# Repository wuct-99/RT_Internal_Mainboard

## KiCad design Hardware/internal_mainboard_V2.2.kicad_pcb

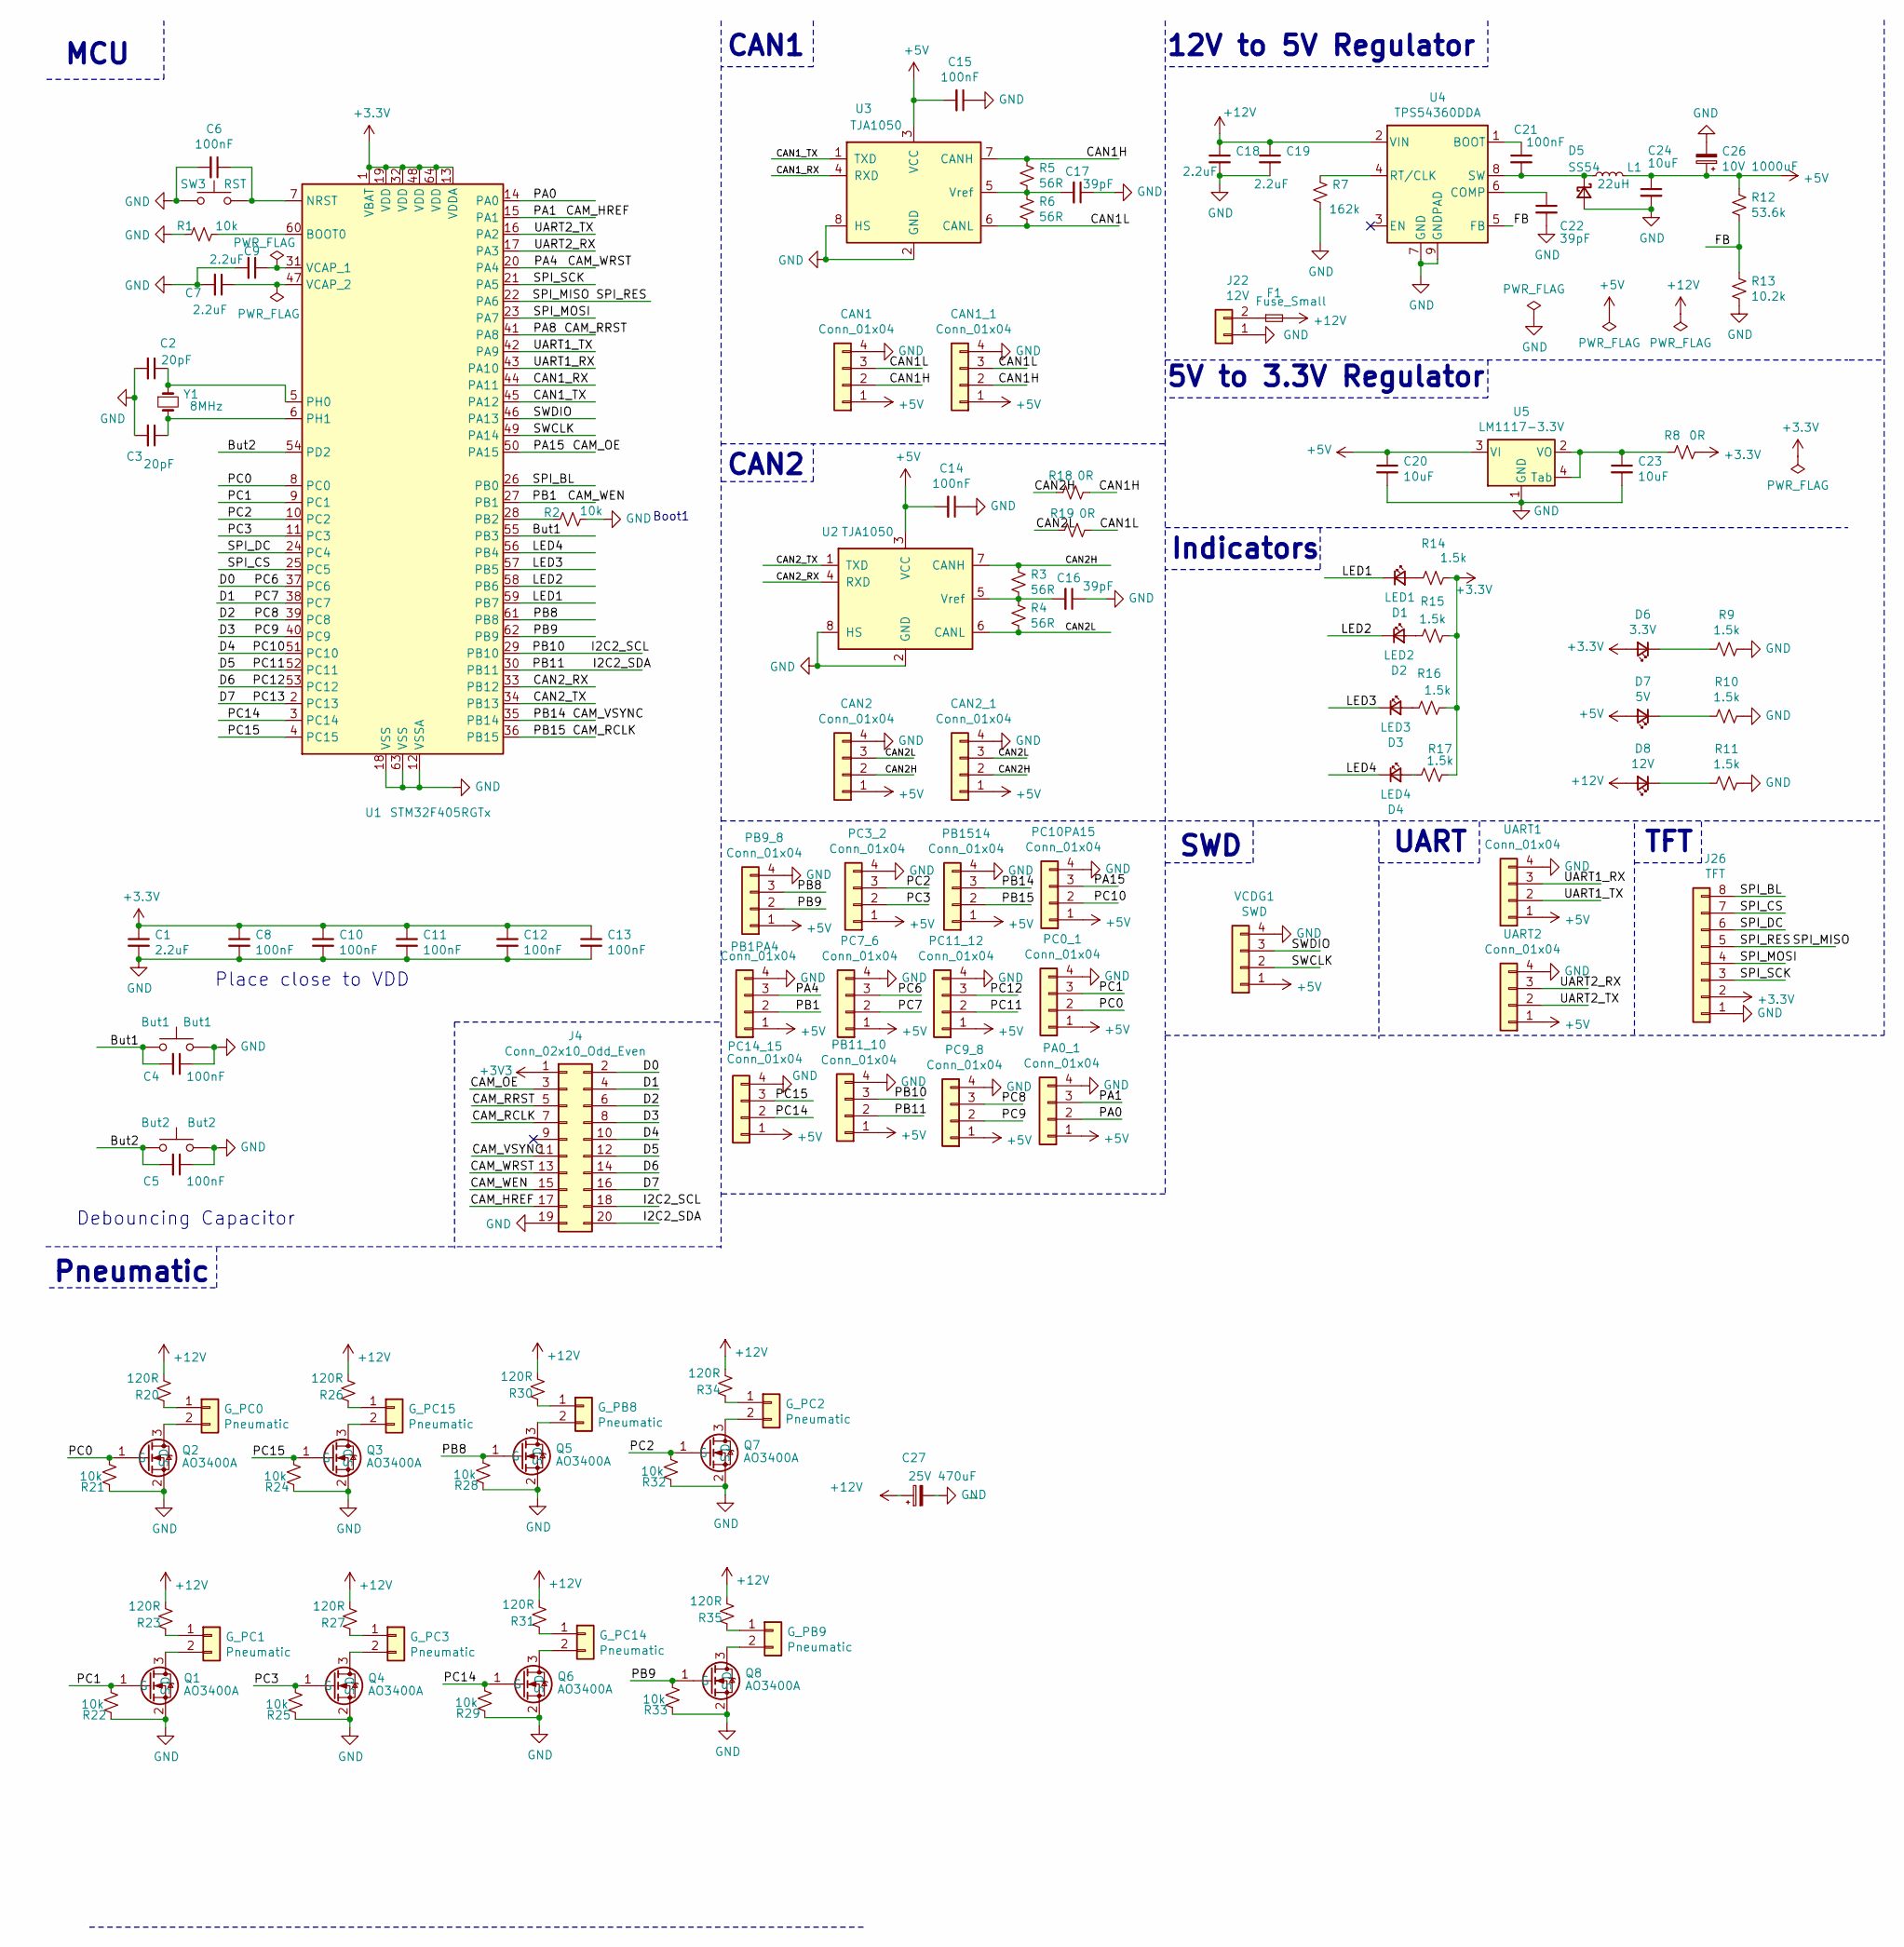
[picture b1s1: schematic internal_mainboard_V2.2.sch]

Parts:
But1: But1; SW_Push
But2: But2; SW_Push
C1, C7, C9, C18, C19: 2.2uF; C_0805_2012Metric_Pad1.18x1.45mm_HandSolder
C2, C3: 20pF; C_0805_2012Metric_Pad1.18x1.45mm_HandSolder
C4, C5, C6, C8, C10, C11, C12, C13, C14, C15, C21: 100nF; C_0805_2012Metric_Pad1.18x1.45mm_HandSolder
C16, C17, C22: 39pF; C_0805_2012Metric_Pad1.18x1.45mm_HandSolder
C20, C23, C24: 10uF; C_0805_2012Metric_Pad1.18x1.45mm_HandSolder
C26: 10V 1000uF; CP_Elec_8x10.5
C27: 25V 470uF; CP_Radial_D8.0mm_P12.00mm
CAN1, CAN1_1, CAN2, CAN2_1: Conn_01x04; Molex_SL_171971-0004_1x04_P2.54mm_Vertical
D1: LED1; LED_0805_2012Metric_Pad1.15x1.40mm_HandSolder
D2: LED2; LED_0805_2012Metric_Pad1.15x1.40mm_HandSolder
D3: LED3; LED_0805_2012Metric_Pad1.15x1.40mm_HandSolder
D4: LED4; LED_0805_2012Metric_Pad1.15x1.40mm_HandSolder
D5: SS54; D_SMB
D6: 3.3V; LED_0805_2012Metric_Pad1.15x1.40mm_HandSolder
D7: 5V; LED_0805_2012Metric_Pad1.15x1.40mm_HandSolder
D8: 12V; LED_0805_2012Metric_Pad1.15x1.40mm_HandSolder
F1: Fuse_Small; Fuse_Blade_ATO_directSolder
G_PB8, G_PB9: Pneumatic; Molex_SL_171971-0002_1x02_P2.54mm_Vertical
G_PC0, G_PC1, G_PC2, G_PC3, G_PC14, G_PC15: Pneumatic; Molex_SL_171971-0002_1x02_P2.54mm_Vertical
J4: Conn_02x10_Odd_Even; PinSocket_2x10_P2.54mm_Vertical
J22: 12V; AMASS_XT30U-M_1x02_P5.0mm_Vertical
J26: TFT; PinSocket_1x08_P2.54mm_Vertical
L1: 22uH; L_7.3x7.3_H3.5
PA0_1: Conn_01x04; Molex_SL_171971-0004_1x04_P2.54mm_Vertical
PB1PA4, PB9_8, PB11_10, PB1514: Conn_01x04; Molex_SL_171971-0004_1x04_P2.54mm_Vertical
PC0_1, PC3_2, PC7_6, PC9_8, PC10PA15, PC11_12, PC14_15: Conn_01x04; Molex_SL_171971-0004_1x04_P2.54mm_Vertical
Q1, Q2, Q3, Q4, Q5, Q6, Q7, Q8: AO3400A; SOT-23
R1, R2, R21, R22, R24, R25, R28, R29, R32, R33: 10k; R_0805_2012Metric_Pad1.20x1.40mm_HandSolder
R3, R4, R5, R6: 56R; R_0805_2012Metric_Pad1.20x1.40mm_HandSolder
R7: 162k; R_0805_2012Metric_Pad1.20x1.40mm_HandSolder
R8, R18, R19: 0R; R_0805_2012Metric_Pad1.20x1.40mm_HandSolder
R9, R10, R11, R14, R15, R16, R17: 1.5k; R_0805_2012Metric_Pad1.20x1.40mm_HandSolder
R12: 53.6k; R_0805_2012Metric_Pad1.20x1.40mm_HandSolder
R13: 10.2k; R_0805_2012Metric_Pad1.20x1.40mm_HandSolder
R20, R23, R26, R27, R30, R31, R34, R35: 120R; R_0805_2012Metric_Pad1.20x1.40mm_HandSolder
SW3: RST; SW_Push
U1: STM32F405RGTx; LQFP-64_10x10mm_P0.5mm
U2, U3: TJA1050; SOIC-8_3.9x4.9mm_P1.27mm
U4: TPS54360DDA; TI_SO-PowerPAD-8_ThermalVias
U5: LM1117-3.3V; SOT-223
UART1, UART2: Conn_01x04; Molex_SL_171971-0004_1x04_P2.54mm_Vertical
VCDG1: SWD; Molex_SL_171971-0004_1x04_P2.54mm_Vertical
Y1: 8MHz; Crystal_HC49-4H_Vertical

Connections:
+5V: C14.2, C15.2, C20.1, C24.1, C26.1, CAN1.1, CAN1_1.1, CAN2.1, CAN2_1.1, D7.2 (A), L1.2, PA0_1.1, PB1PA4.1, PB9_8.1, PB11_10.1, PB1514.1, PC0_1.1, PC3_2.1, PC7_6.1, PC9_8.1, PC10PA15.1, PC11_12.1, PC14_15.1, R12.1, U2.3 (VCC), U3.3 (VCC), U5.3 (VI), UART1.1, UART2.1, VCDG1.1; also elsewhere on the board
+12V: C18.1, C19.1, C27.1, D8.2 (A), F1.2, R20.2, R23.2, R26.2, R27.2, R30.2, R31.2, R34.2, R35.2, U4.2 (VIN)
/But1: But1.1, C4.2, U1.55 (PB3)
/But2: But2.1, C5.2, U1.54 (PD2)
/CAM_HREF: J4.17, PA0_1.3, U1.15 (PA1)
/CAM_OE: J4.3, PC10PA15.3, U1.50 (PA15)
/CAM_RCLK: J4.7, PB1514.2, U1.36 (PB15)
/CAM_RRST: J4.5, U1.41 (PA8)
/CAM_VSYNC: J4.11, PB1514.3, U1.35 (PB14)
/CAM_WEN: J4.15, PB1PA4.2, U1.27 (PB1)
/CAM_WRST: J4.13, PB1PA4.3, U1.20 (PA4)
/CAN1H: CAN1.2, CAN1_1.2, R5.2, R18.1, U3.7 (CANH)
/CAN1L: CAN1.3, CAN1_1.3, R6.2, R19.1, U3.6 (CANL)
/CAN1_RX: U1.44 (PA11), U3.4 (RXD)
/CAN1_TX: U1.45 (PA12), U3.1 (TXD)
/CAN2H: CAN2.2, CAN2_1.2, R3.2, R18.2, U2.7 (CANH)
/CAN2L: CAN2.3, CAN2_1.3, R4.2, R19.2, U2.6 (CANL)
/CAN2_RX: U1.33 (PB12), U2.4 (RXD)
/CAN2_TX: U1.34 (PB13), U2.1 (TXD)
/D0: J4.2, PC7_6.3, U1.37 (PC6)
/D1: J4.4, PC7_6.2, U1.38 (PC7)
/D2: J4.6, PC9_8.3, U1.39 (PC8)
/D3: J4.8, PC9_8.2, U1.40 (PC9)
/D4: J4.10, PC10PA15.2, U1.51 (PC10)
/D5: J4.12, PC11_12.2, U1.52 (PC11)
/D6: J4.14, PC11_12.3, U1.53 (PC12)
/D7: J4.16, U1.2 (PC13)
/FB: R12.2, R13.1, U4.5 (FB)
/I2C2_SCL: J4.18, PB11_10.3, U1.29 (PB10)
/I2C2_SDA: J4.20, PB11_10.2, U1.30 (PB11)
/LED1: D1.1 (K), U1.59 (PB7)
/LED2: D2.1 (K), U1.58 (PB6)
/LED3: D3.1 (K), U1.57 (PB5)
/LED4: D4.1 (K), U1.56 (PB4)
/PA0: PA0_1.2, U1.14 (PA0)
/PB8: PB9_8.3, Q5.1 (G), R28.2, U1.61 (PB8)
/PB9: PB9_8.2, Q8.1 (G), R33.2, U1.62 (PB9)
/PC0: PC0_1.2, Q2.1 (G), R21.2, U1.8 (PC0)
/PC1: PC0_1.3, Q1.1 (G), R22.2, U1.9 (PC1)
/PC2: PC3_2.3, Q7.1 (G), R32.2, U1.10 (PC2)
/PC3: PC3_2.2, Q4.1 (G), R25.2, U1.11 (PC3)
/PC14: PC14_15.2, Q6.1 (G), R29.2, U1.3 (PC14)
/PC15: PC14_15.3, Q3.1 (G), R24.2, U1.4 (PC15)
/SPI_BL: J26.8, U1.26 (PB0)
/SPI_CS: J26.7, U1.25 (PC5)
/SPI_DC: J26.6, U1.24 (PC4)
/SPI_MISO: J26.5, U1.22 (PA6)
/SPI_MOSI: J26.4, U1.23 (PA7)
/SPI_SCK: J26.3, U1.21 (PA5)
/SWCLK: U1.49 (PA14), VCDG1.2; also elsewhere on the board
/SWDIO: U1.46 (PA13), VCDG1.3; also elsewhere on the board
/UART1_RX: U1.43 (PA10), UART1.3
/UART1_TX: U1.42 (PA9), UART1.2
/UART2_RX: U1.17 (PA3), UART2.3
/UART2_TX: U1.16 (PA2), UART2.2
GND: But1.2, But2.2, C1.2, C2.2, C3.2, C4.1, C5.1, C6.2, C7.2, C8.2, C9.2, C10.2, C11.2, C12.2, C13.2, C14.1, C15.1, C16.1, C17.1, C18.2, C19.2, C20.2, C22.2, C23.2, C24.2, C26.2, C27.2, CAN1.4, CAN1_1.4, CAN2.4, CAN2_1.4, D5.2 (A), J4.19, J22.1, J26.1, PA0_1.4, PB1PA4.4, PB9_8.4, PB11_10.4, PB1514.4, PC0_1.4, PC3_2.4, PC7_6.4, PC9_8.4, PC10PA15.4, PC11_12.4, PC14_15.4, Q1.2 (S), Q2.2 (S), Q3.2 (S), Q4.2 (S), Q5.2 (S), Q6.2 (S), Q7.2 (S), Q8.2 (S), R1.2, R2.1, R7.2, R9.1, R10.1, R11.1, R13.2, R21.1, R22.1, R24.1, R25.1, R28.1, R29.1, R32.1, R33.1, SW3.1, U1.12 (VSSA), U1.18 (VSS), U1.63 (VSS), U2.2 (GND), U2.8 (HS), U3.2 (GND), U3.8 (HS), U4.7 (GND), U4.9 (GNDPAD), U5.1 (GND), UART1.4, UART2.4, VCDG1.4; also elsewhere on the board
unnamed: C2.1, U1.5 (PH0), Y1.1
unnamed: C3.1, U1.6 (PH1), Y1.2
unnamed 58: C6.1, SW3.2, U1.7 (NRST); also elsewhere on the board
unnamed: C7.1, U1.47 (VCAP_2)
unnamed: C9.1, U1.31 (VCAP_1)
unnamed: C16.2, R3.1, R4.1, U2.5 (Vref)
unnamed: C17.2, R5.1, R6.1, U3.5 (Vref)
unnamed: C21.1, U4.1 (BOOT)
unnamed: C21.2, D5.1 (K), L1.1, U4.8 (SW)
unnamed: C22.1, U4.6 (COMP)
unnamed: C23.1, R8.2, U5.2 (VO), U5.4 (Tab)
unnamed: D1.2 (A), R14.2
unnamed: D2.2 (A), R15.2
unnamed: D3.2 (A), R16.2
unnamed: D4.2 (A), R17.2
unnamed: D6.1 (K), R9.2
unnamed: D7.1 (K), R10.2
unnamed: D8.1 (K), R11.2
unnamed: F1.1, J22.2
unnamed: G_PB8.1, R30.1
unnamed: G_PB8.2, Q5.3 (D)
unnamed: G_PB9.1, R35.1
unnamed: G_PB9.2, Q8.3 (D)
unnamed: G_PC0.1, R20.1
unnamed: G_PC0.2, Q2.3 (D)
unnamed: G_PC1.1, R23.1
unnamed: G_PC1.2, Q1.3 (D)
unnamed: G_PC2.1, R34.1
unnamed: G_PC2.2, Q7.3 (D)
unnamed: G_PC3.1, R27.1
unnamed: G_PC3.2, Q4.3 (D)
unnamed: G_PC14.1, R31.1
unnamed: G_PC14.2, Q6.3 (D)
unnamed: G_PC15.1, R26.1
unnamed: G_PC15.2, Q3.3 (D)
unnamed: R1.1, U1.60 (BOOT0)
unnamed: R2.2, U1.28 (PB2)
unnamed: R7.1, U4.4 (RT/CLK)

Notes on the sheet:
Place close to VDD
Debouncing Capacitor
12V to 5V Regulator
5V to 3.3V Regulator
Indicators
CAN1
CAN2
UART
TFT
SWD
Boot1
MCU
Pneumatic

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
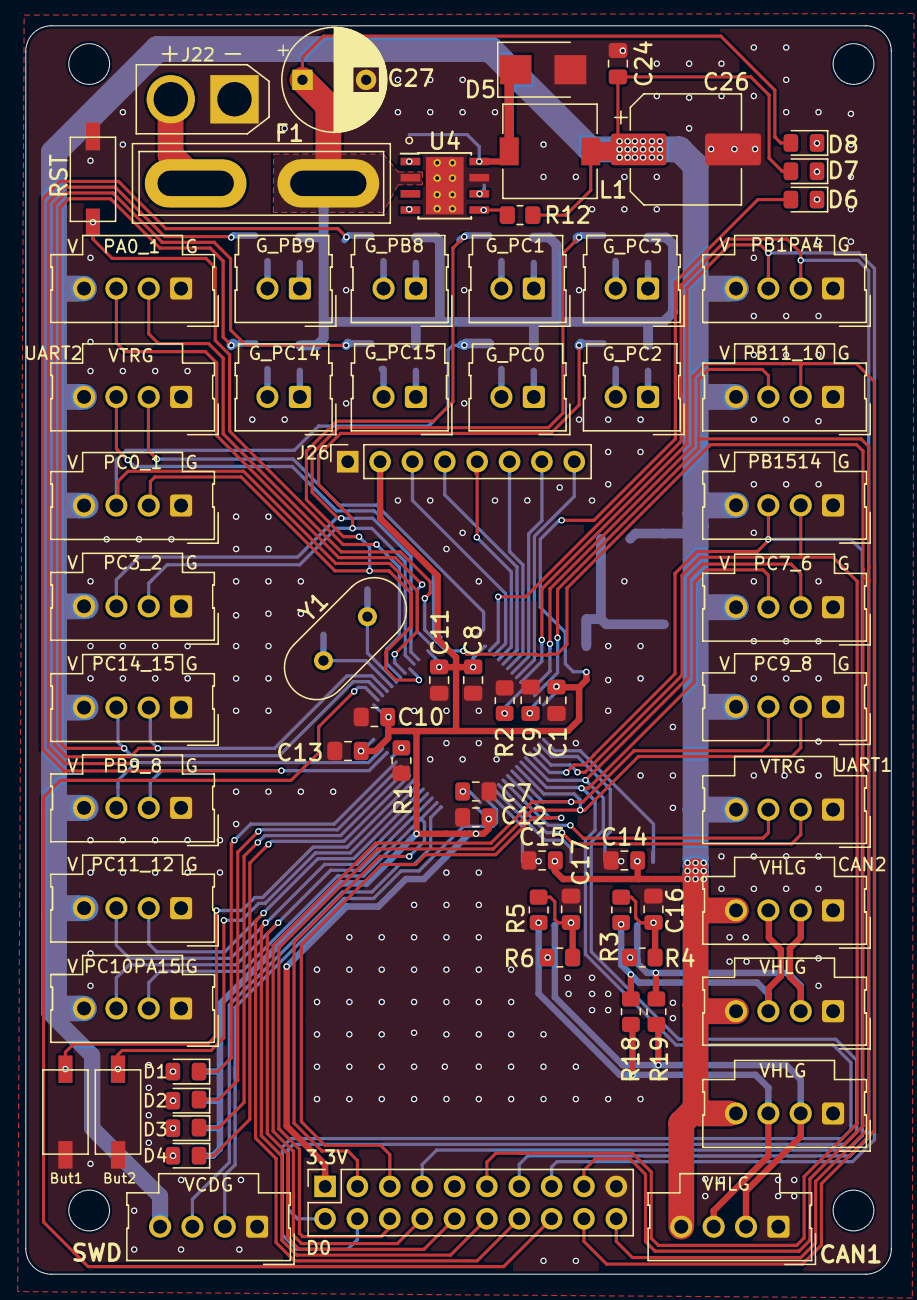
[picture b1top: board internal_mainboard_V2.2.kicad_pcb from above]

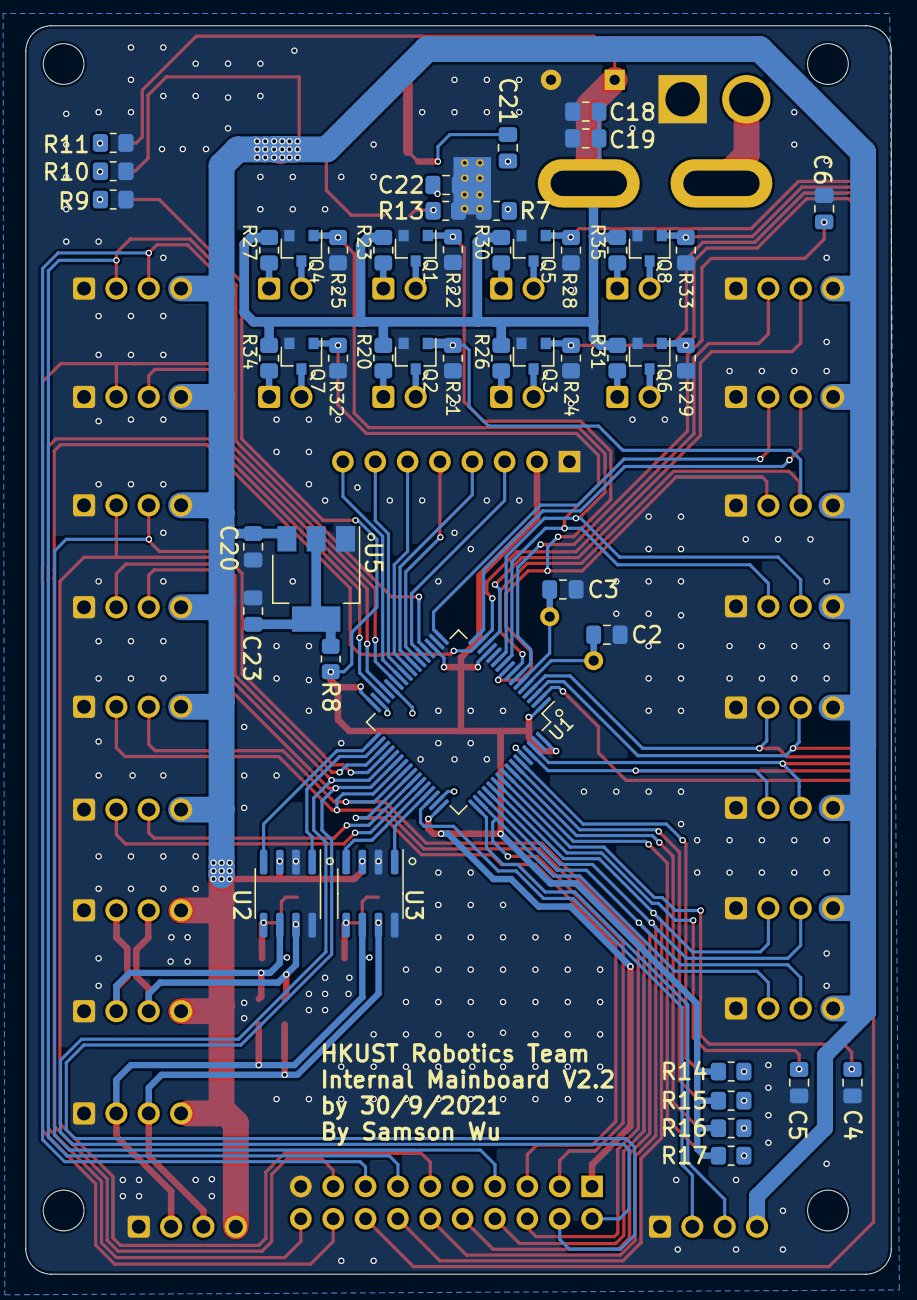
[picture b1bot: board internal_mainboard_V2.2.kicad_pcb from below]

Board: 2 copper layers, 67.9 x 98.0 mm, 118 parts (49 on the bottom side), 95 nets.

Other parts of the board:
RST: RST; SW_Push
SWD: SWD; Molex_SL_171971-0004_1x04_P2.54mm_Vertical

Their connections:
+5V: SWD.1; also elsewhere on the board
/SWCLK: SWD.2; also elsewhere on the board
/SWDIO: SWD.3; also elsewhere on the board
GND: RST.1, SWD.4; also elsewhere on the board
unnamed 58: RST.2; also elsewhere on the board

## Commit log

2021-10-30 hardware
